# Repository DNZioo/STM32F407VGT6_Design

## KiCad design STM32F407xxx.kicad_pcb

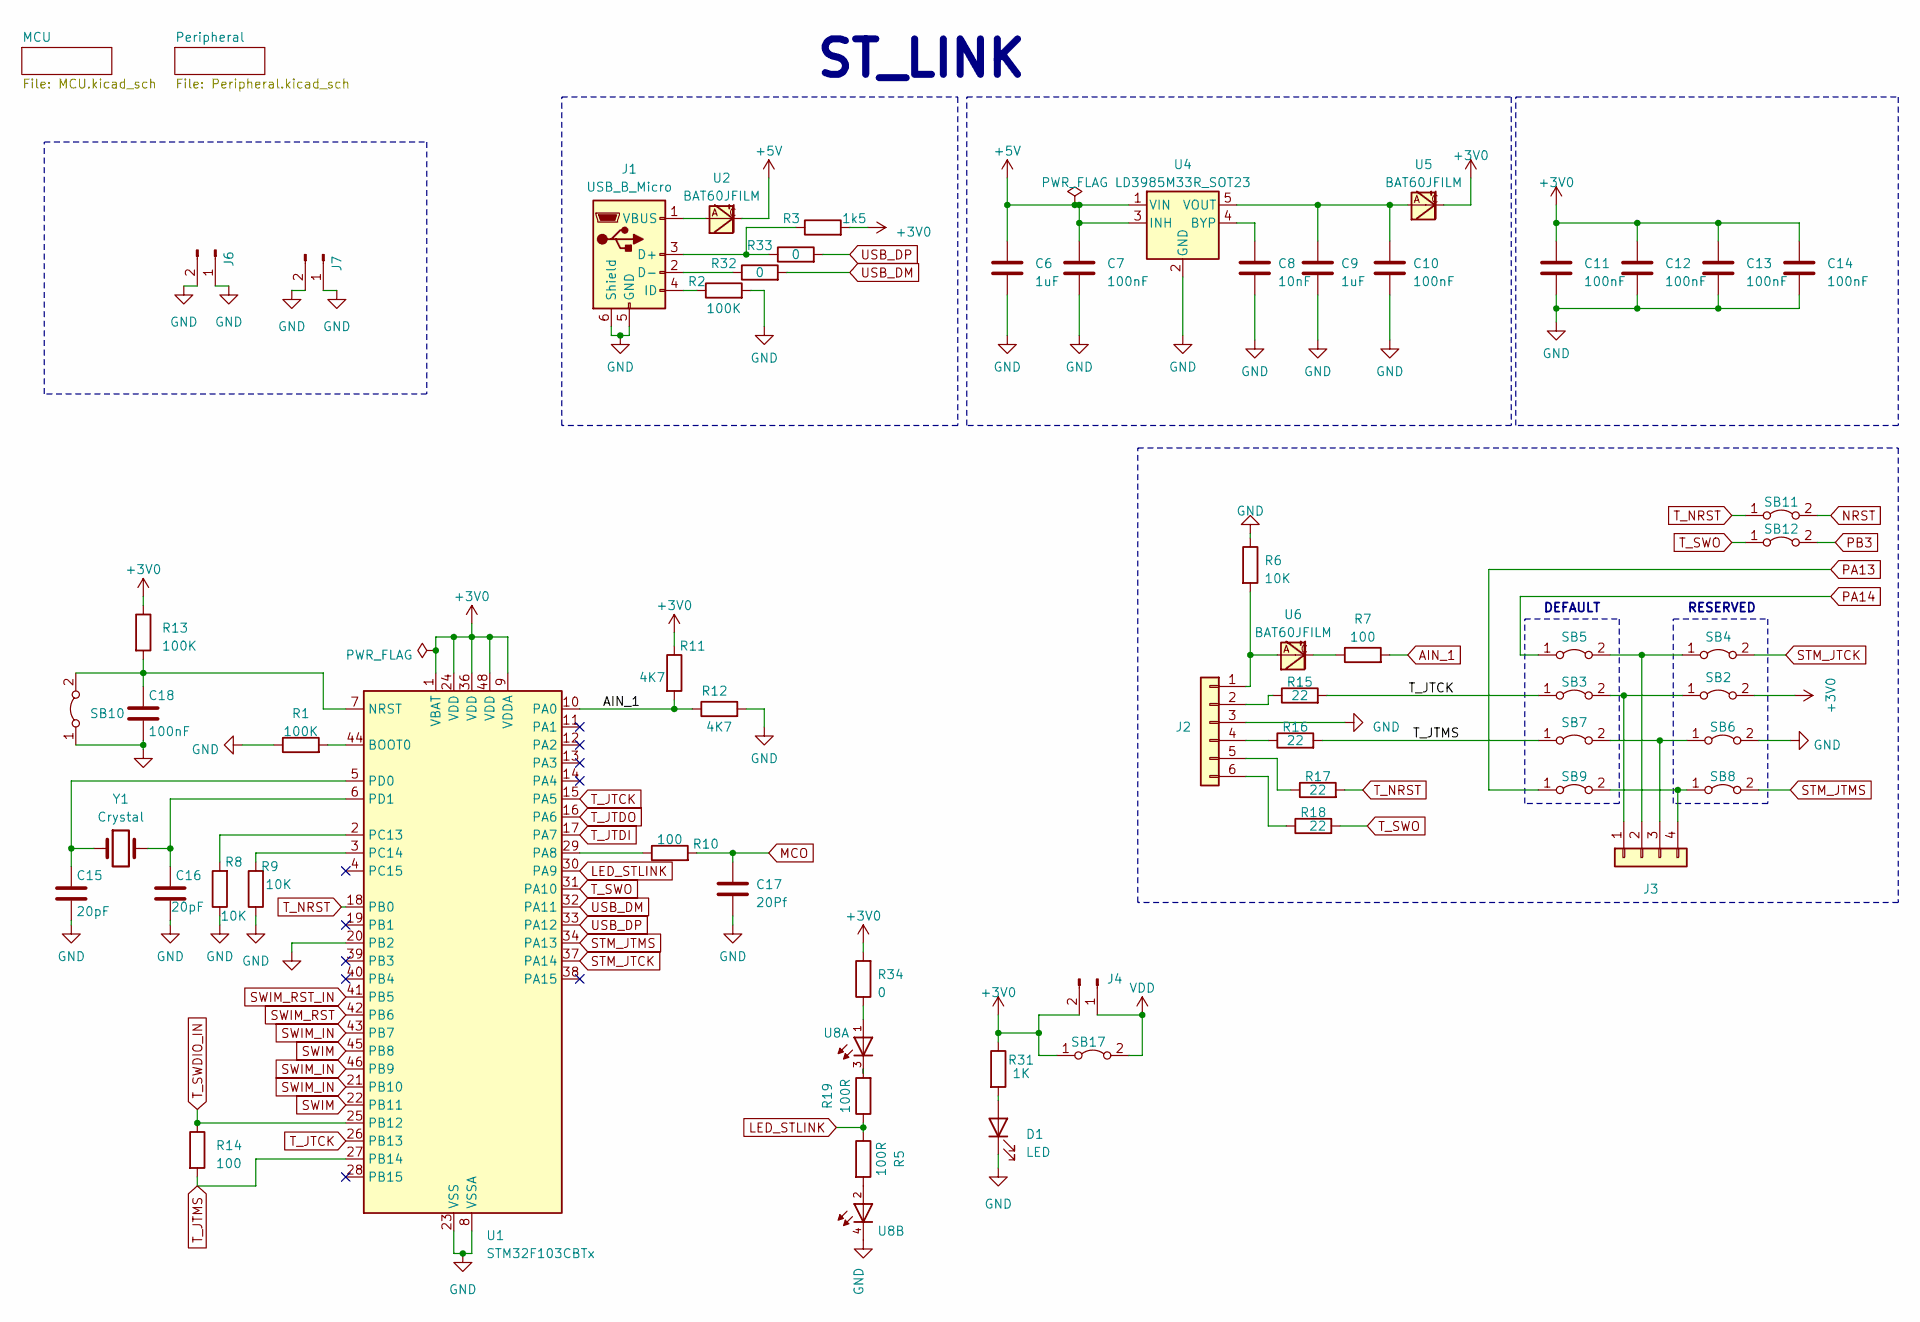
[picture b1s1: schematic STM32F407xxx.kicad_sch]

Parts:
C6, C9: 1uF; C_0603_1608Metric
C7, C10, C11, C12, C13, C14, C18: 100nF; C_0603_1608Metric
C8: 10nF; C_0603_1608Metric
C15, C16: 20pF; C_0603_1608Metric
C17: 20Pf; C_0603_1608Metric
D1: LED; LED_0603_1608Metric
J1: USB_B_Micro; usb_mini
J2: Conn_01x06; PinHeader_1x06_P2.54mm_Vertical
J3: Conn_01x04; PinHeader_1x04_P2.54mm_Vertical
J4, J6, J7: Conn_01x02_Pin; PinHeader_1x02_P2.54mm_Vertical
R1, R2, R13: 100K; R_0603_1608Metric
R3: 1k5; R_0603_1608Metric
R5, R19: 100R; R_0603_1608Metric
R6, R8, R9: 10K; R_0603_1608Metric
R7, R10, R14: 100; R_0603_1608Metric
R11, R12: 4K7; R_0603_1608Metric
R15, R16, R17, R18: 22; R_0603_1608Metric
R31: 1K; R_0603_1608Metric
R32, R33, R34: 0; R_0603_1608Metric
SB2, SB3, SB4, SB5, SB6, SB7, SB8, SB9, SB10, SB11, SB12, SB17: Jumper_2_Bridged; SolderJumper-2_P1.3mm_Open_TrianglePad1.0x1.5mm
U1: STM32F103CBTx; LQFP-48_7x7mm_P0.5mm
U2, U5, U6: BAT60JFILM; SOD323
U4: LD3985M33R_SOT23; SOT-23-5
U8: 150141RB73100; 3528
Y1: Crystal; Crystal_HC49-4H_Vertical

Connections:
+3V0: C11.1, C12.1, C13.1, C14.1, J4.2, R3.2, R11.1, R13.1, R31.1, R34.2, SB2.2 (B), SB17.1 (A), U1.1 (VBAT), U1.9 (VDDA), U1.24 (VDD), U1.36 (VDD), U1.48 (VDD), U5.C; also elsewhere on the board
+5V: C6.1, C7.1, U2.C, U4.1 (VIN), U4.3 (INH); also elsewhere on the board
AIN_1: R7.2, R11.2, R12.1, U1.10 (PA0)
GND: C6.2, C7.2, C8.2, C9.2, C10.2, C11.2, C12.2, C13.2, C14.2, C15.2, C16.2, C17.2, C18.2, D1.1 (K), J1.5 (GND), J1.6 (Shield), J2.3, J6.1, J6.2, J7.1, J7.2, R1.1, R2.2, R6.1, R8.1, R9.1, R12.2, SB6.2 (B), SB10.1 (A), U1.8 (VSSA), U1.20 (PB2), U1.23 (VSS), U1.35 (VSS), U1.47 (VSS), U4.2 (GND), U8.4; also elsewhere on the board
LED_STLINK: R5.1, R19.1, U1.30 (PA9)
MCO: C17.1, R10.2; also elsewhere on the board
NRST: SB11.2 (B); also elsewhere on the board
unnamed: D1.2 (A), R31.2
unnamed: J1.3 (D+), R3.1, R33.1
unnamed: J1.2 (D-), R32.1
unnamed: J1.4 (ID), R2.1
unnamed: J1.1 (VBUS), U2.A
unnamed: J2.1, R6.2, U6.A
unnamed: J2.2, R15.1
unnamed: J2.4, R16.1
unnamed: J2.5, R17.1
unnamed: J2.6, R18.1
unnamed: J3.1, SB2.1 (A), SB3.2 (B)
unnamed: J3.2, SB4.1 (A), SB5.2 (B)
unnamed: J3.3, SB6.1 (A), SB7.2 (B)
unnamed: J3.4, SB8.1 (A), SB9.2 (B)
unnamed: R5.2, U8.2
unnamed: R7.1, U6.C
unnamed: R19.2, U8.3
unnamed: R34.1, U8.1
unnamed: C18.1, R13.2, SB10.2 (B), U1.7 (NRST)
unnamed: R1.2, U1.44 (BOOT0)
unnamed: R10.1, U1.29 (PA8)
unnamed: R8.2, U1.2 (PC13)
unnamed: R9.2, U1.3 (PC14)
unnamed: C15.1, U1.5 (PD0), Y1.1
unnamed: C16.1, U1.6 (PD1), Y1.2
unnamed: C8.1, U4.4 (BYP)
unnamed: C9.1, C10.1, U4.5 (VOUT), U5.A
PA13: SB9.1 (A); also elsewhere on the board
PA14: SB5.1 (A); also elsewhere on the board
PB3: SB12.2 (B); also elsewhere on the board
STM_JTCK: SB4.2 (B), U1.37 (PA14)
STM_JTMS: SB8.2 (B), U1.34 (PA13)
SWIM: U1.22 (PB11), U1.45 (PB8)
SWIM_IN: U1.21 (PB10), U1.43 (PB7), U1.46 (PB9)
SWIM_RST: U1.42 (PB6)
SWIM_RST_IN: U1.41 (PB5)
T_JTCK: R15.2, SB3.1 (A), U1.15 (PA5), U1.26 (PB13)
T_JTDI: U1.17 (PA7)
T_JTDO: U1.16 (PA6)
T_JTMS: R14.2, R16.2, SB7.1 (A), U1.27 (PB14)
T_NRST: R17.2, SB11.1 (A), U1.18 (PB0)
T_SWDIO_IN: R14.1, U1.25 (PB12)
T_SWO: R18.2, SB12.1 (A), U1.31 (PA10)
USB_DM: R32.2, U1.32 (PA11)
USB_DP: R33.2, U1.33 (PA12)
VDD: J4.1, SB17.2 (B); also elsewhere on the board

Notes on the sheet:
DEFAULT
ST_LINK
RESERVED

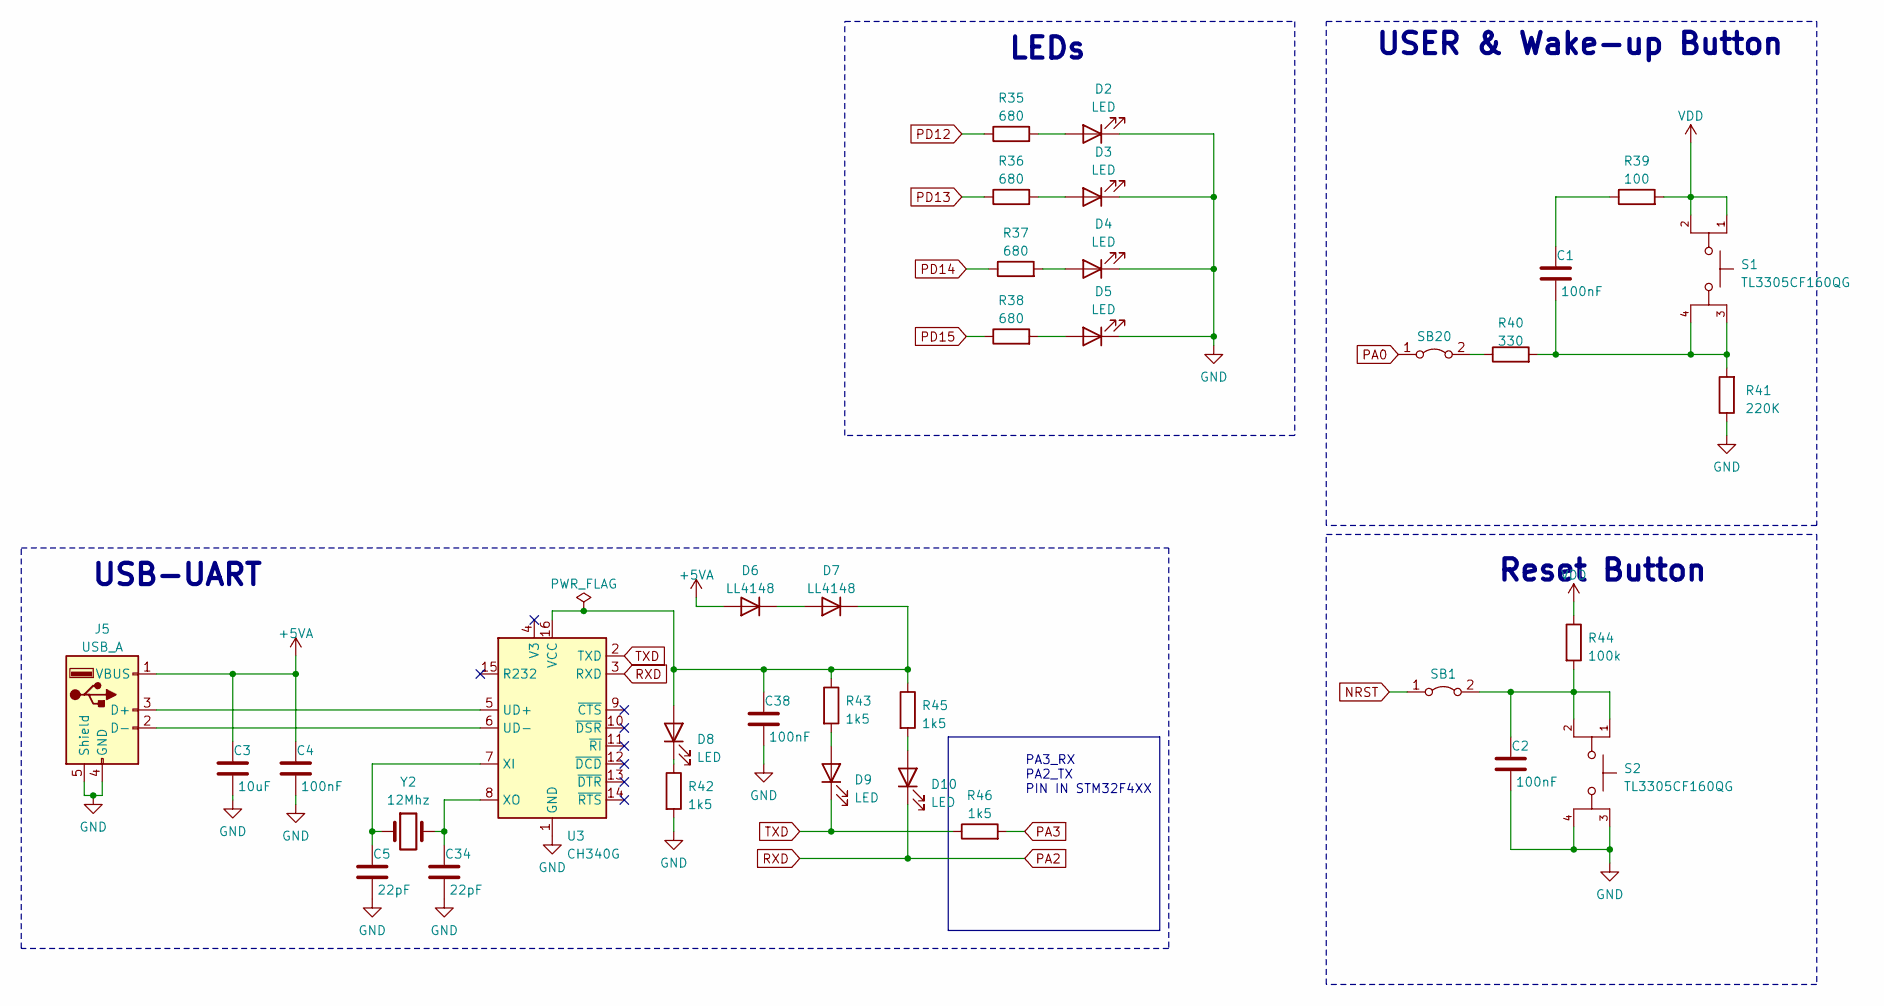
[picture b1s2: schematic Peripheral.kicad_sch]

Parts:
C1, C2, C4, C38: 100nF; C_0603_1608Metric
C3: 10uF; C_0603_1608Metric
C5, C34: 22pF; C_0603_1608Metric
D2, D3, D4, D5, D8, D9, D10: LED; LED_0603_1608Metric
D6, D7: LL4148; D_MiniMELF
J5: USB_A; TE_1981584-1
R35, R36, R37, R38: 680; R_0603_1608Metric
R39: 100; R_0603_1608Metric
R40: 330; R_0603_1608Metric
R41: 220K; R_0603_1608Metric
R42, R43, R45, R46: 1k5; R_0603_1608Metric
R44: 100k; R_0603_1608Metric
S1, S2: TL3305CF160QG; SW_TL3305CF160QG; PARTREV C
SB1, SB20: Jumper_2_Bridged; SolderJumper-2_P1.3mm_Open_TrianglePad1.0x1.5mm
U3: CH340G; SOIC-16_3.9x9.9mm_P1.27mm
Y2: 12Mhz; Crystal_HC49-4H_Vertical

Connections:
+5VA: C3.1, C4.1, D6.2 (A), J5.1 (VBUS)
GND: C2.1, C3.2, C4.2, C5.2, C34.2, C38.2, D2.1 (K), D3.1 (K), D4.1 (K), D5.1 (K), J5.4 (GND), J5.5 (Shield), R41.1, R42.2, S2.3, S2.4, U3.1 (GND); also elsewhere on the board
NRST: SB1.1 (A); also elsewhere on the board
unnamed: C1.1, R40.2, R41.2, S1.3, S1.4
unnamed: C1.2, R39.1
unnamed: D2.2 (A), R35.2
unnamed: D3.2 (A), R36.2
unnamed: D4.2 (A), R37.2
unnamed: D5.2 (A), R38.2
unnamed: D6.1 (K), D7.2 (A)
unnamed: C38.1, D7.1 (K), D8.2 (A), R43.1, R45.1, U3.16 (VCC)
unnamed: D8.1 (K), R42.1
unnamed: D9.2 (A), R43.2
unnamed: D10.2 (A), R45.2
unnamed: J5.3 (D+), U3.5 (UD+)
unnamed: J5.2 (D-), U3.6 (UD-)
unnamed: C2.2, R44.2, S2.1, S2.2, SB1.2 (B)
unnamed: R40.1, SB20.2 (B)
unnamed: C5.1, U3.7 (XI), Y2.1
unnamed: C34.1, U3.8 (XO), Y2.2
PA0: SB20.1 (A); also elsewhere on the board
PA2: D10.1 (K), U3.3 (RXD); also elsewhere on the board
PA3: R46.2; also elsewhere on the board
PD12: R35.1; also elsewhere on the board
PD13: R36.1; also elsewhere on the board
PD14: R37.1; also elsewhere on the board
PD15: R38.1; also elsewhere on the board
TXD: D9.1 (K), R46.1, U3.2 (TXD)
VDD: R39.2, R44.1, S1.1, S1.2; also elsewhere on the board

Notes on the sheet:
LEDs
USER & Wake-up Button
USB-UART
PA3_RX PA2_TX PIN IN STM32F4XX
Reset Button

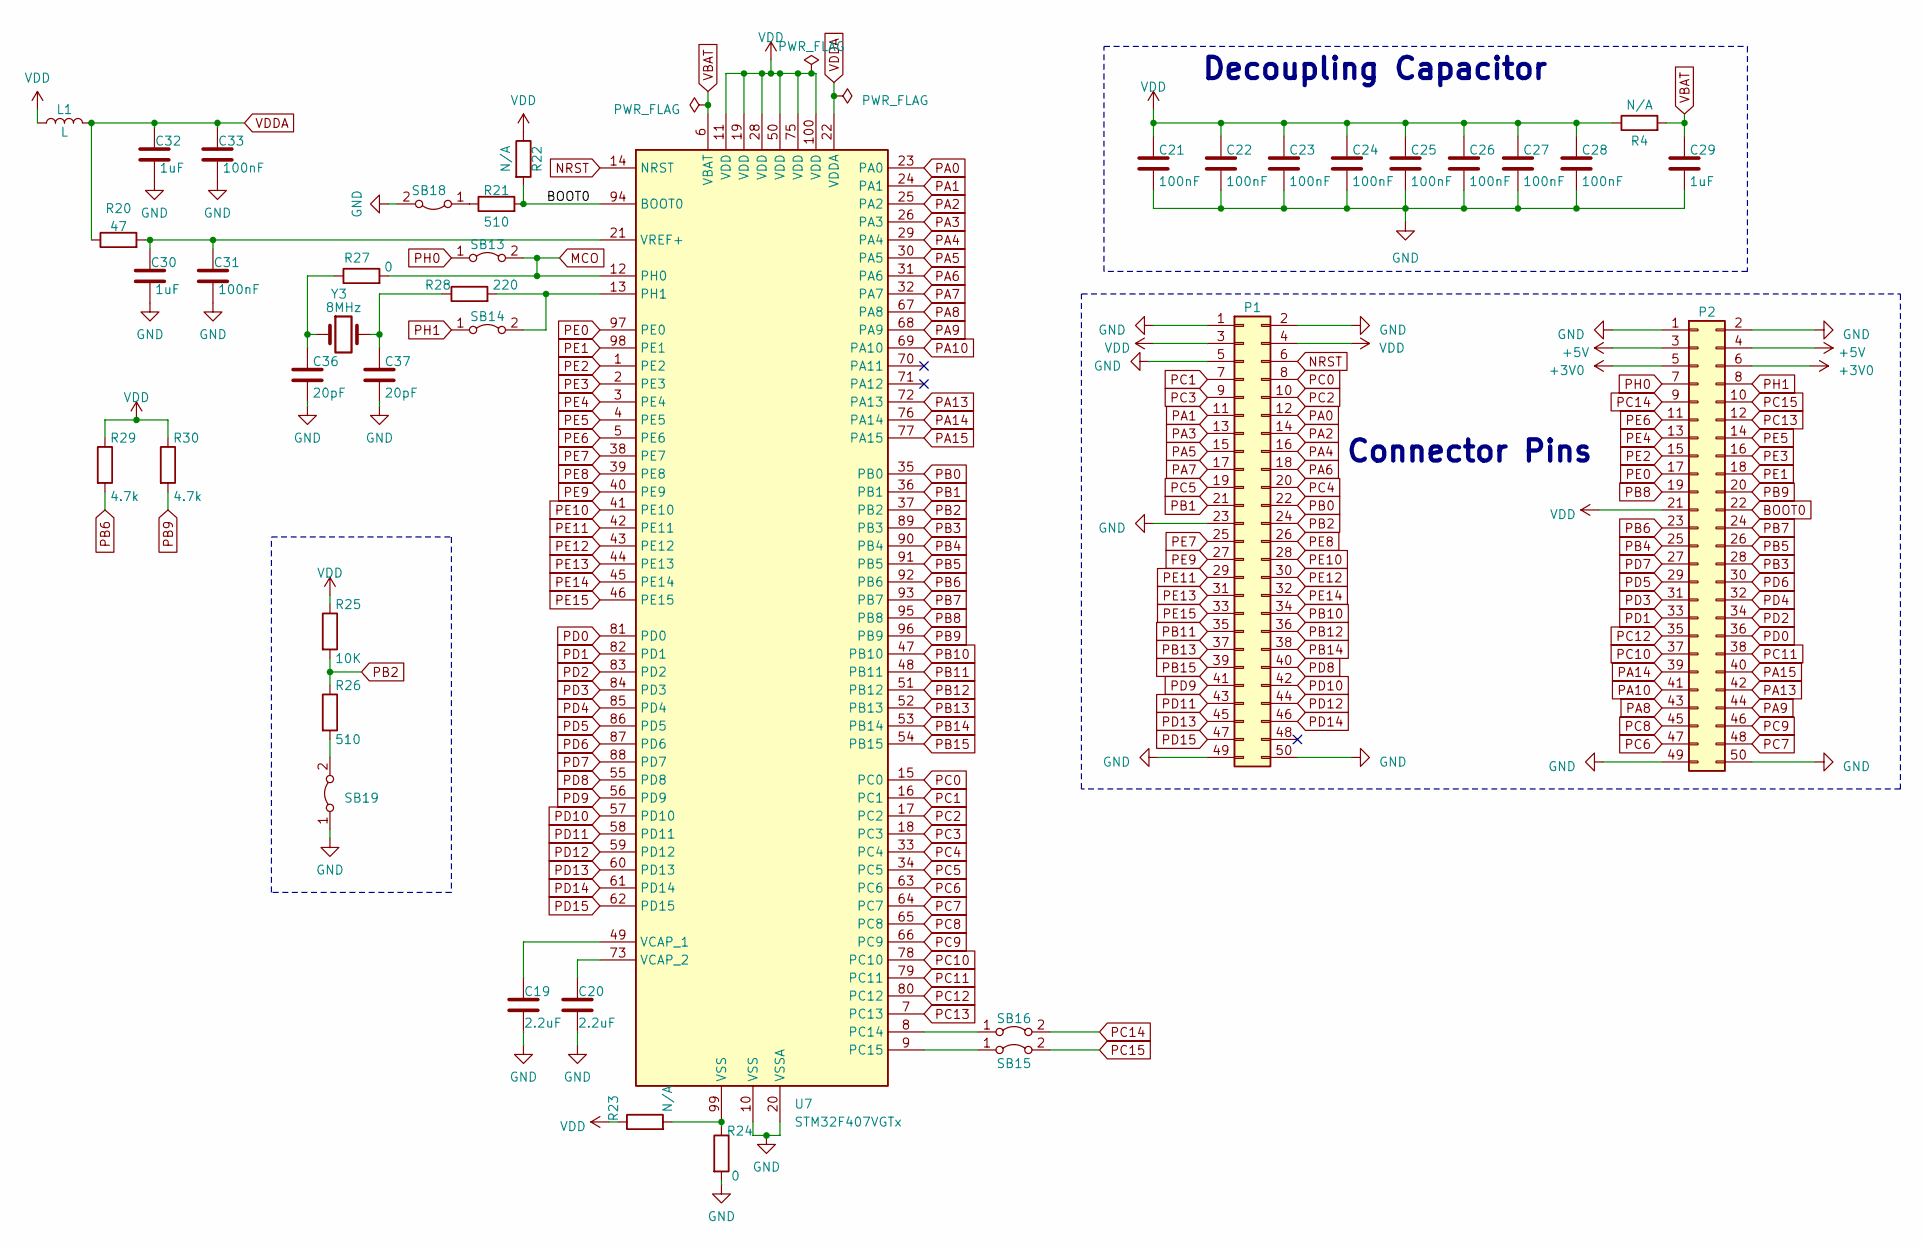
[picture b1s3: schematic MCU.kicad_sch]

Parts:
C19, C20: 2.2uF; C_0603_1608Metric
C21, C22, C23, C24, C25, C26, C27, C28, C31, C33: 100nF; C_0603_1608Metric
C29, C30, C32: 1uF; C_0603_1608Metric
C36, C37: 20pF; C_0603_1608Metric
L1: L; L_0603_1608Metric
P1, P2: Conn_02x25_Odd_Even; PinHeader_2x25_P2.54mm_Vertical
R4, R22, R23: N/A; R_0603_1608Metric
R20: 47; R_0603_1608Metric
R21, R26: 510; R_0603_1608Metric
R24, R27: 0; R_0603_1608Metric
R25: 10K; R_0603_1608Metric
R28: 220; R_0603_1608Metric
R29, R30: 4.7k; R_0603_1608Metric
SB13, SB14, SB15, SB16, SB18, SB19: Jumper_2_Bridged; SolderJumper-2_P1.3mm_Open_TrianglePad1.0x1.5mm
U7: STM32F407VGTx; LQFP-100_14x14mm_P0.5mm
Y3: 8MHz; Crystal_HC49-4H_Vertical

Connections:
+3V0: P2.5, P2.6; also elsewhere on the board
+5V: P2.3, P2.4; also elsewhere on the board
BOOT0: P2.22, R21.2, R22.2, U7.94 (BOOT0)
GND: C19.2, C20.2, C21.2, C22.2, C23.2, C24.2, C25.2, C26.2, C27.2, C28.2, C29.2, C30.2, C31.2, C32.2, C33.2, C36.2, C37.2, P1.1, P1.2, P1.5, P1.23, P1.49, P1.50, P2.1, P2.2, P2.49, P2.50, R24.2, SB18.2 (B), SB19.1 (A), U7.10 (VSS), U7.20 (VSSA), U7.27 (VSS), U7.74 (VSS); also elsewhere on the board
MCO: R27.2, SB13.2 (B), U7.12 (PH0); also elsewhere on the board
NRST: P1.6, U7.14 (NRST); also elsewhere on the board
unnamed: C36.1, R27.1, Y3.1
unnamed: C37.1, R28.1, Y3.2
unnamed: R23.2, R24.1, U7.99 (VSS)
unnamed: R28.2, SB14.2 (B), U7.13 (PH1)
unnamed: SB15.1 (A), U7.9 (PC15)
unnamed: SB16.1 (A), U7.8 (PC14)
unnamed: R21.1, SB18.1 (A)
unnamed: R26.2, SB19.2 (B)
unnamed: C19.1, U7.49 (VCAP_1)
unnamed: C20.1, U7.73 (VCAP_2)
unnamed: C30.1, C31.1, R20.2, U7.21 (VREF+)
PA0: P1.12, U7.23 (PA0); also elsewhere on the board
PA1: P1.11, U7.24 (PA1)
PA2: P1.14, U7.25 (PA2); also elsewhere on the board
PA3: P1.13, U7.26 (PA3); also elsewhere on the board
PA4: P1.16, U7.29 (PA4)
PA5: P1.15, U7.30 (PA5)
PA6: P1.18, U7.31 (PA6)
PA7: P1.17, U7.32 (PA7)
PA8: P2.43, U7.67 (PA8)
PA9: P2.44, U7.68 (PA9)
PA10: P2.41, U7.69 (PA10)
PA13: P2.42, U7.72 (PA13); also elsewhere on the board
PA14: P2.39, U7.76 (PA14); also elsewhere on the board
PA15: P2.40, U7.77 (PA15)
PB0: P1.22, U7.35 (PB0)
PB1: P1.21, U7.36 (PB1)
PB2: P1.24, R25.2, R26.1, U7.37 (PB2)
PB3: P2.28, U7.89 (PB3); also elsewhere on the board
PB4: P2.25, U7.90 (PB4)
PB5: P2.26, U7.91 (PB5)
PB6: P2.23, R29.2, U7.92 (PB6)
PB7: P2.24, U7.93 (PB7)
PB8: P2.19, U7.95 (PB8)
PB9: P2.20, R30.2, U7.96 (PB9)
PB10: P1.34, U7.47 (PB10)
PB11: P1.35, U7.48 (PB11)
PB12: P1.36, U7.51 (PB12)
PB13: P1.37, U7.52 (PB13)
PB14: P1.38, U7.53 (PB14)
PB15: P1.39, U7.54 (PB15)
PC0: P1.8, U7.15 (PC0)
PC1: P1.7, U7.16 (PC1)
PC2: P1.10, U7.17 (PC2)
PC3: P1.9, U7.18 (PC3)
PC4: P1.20, U7.33 (PC4)
PC5: P1.19, U7.34 (PC5)
PC6: P2.47, U7.63 (PC6)
PC7: P2.48, U7.64 (PC7)
PC8: P2.45, U7.65 (PC8)
PC9: P2.46, U7.66 (PC9)
PC10: P2.37, U7.78 (PC10)
PC11: P2.38, U7.79 (PC11)
PC12: P2.35, U7.80 (PC12)
PC13: P2.12, U7.7 (PC13)
PC14: P2.9, SB16.2 (B)
PC15: P2.10, SB15.2 (B)
PD0: P2.36, U7.81 (PD0)
PD1: P2.33, U7.82 (PD1)
PD2: P2.34, U7.83 (PD2)
PD3: P2.31, U7.84 (PD3)
PD4: P2.32, U7.85 (PD4)
PD5: P2.29, U7.86 (PD5)
PD6: P2.30, U7.87 (PD6)
PD7: P2.27, U7.88 (PD7)
PD8: P1.40, U7.55 (PD8)
PD9: P1.41, U7.56 (PD9)
PD10: P1.42, U7.57 (PD10)
PD11: P1.43, U7.58 (PD11)
PD12: P1.44, U7.59 (PD12); also elsewhere on the board
PD13: P1.45, U7.60 (PD13); also elsewhere on the board
PD14: P1.46, U7.61 (PD14); also elsewhere on the board
PD15: P1.47, U7.62 (PD15); also elsewhere on the board
PE0: P2.17, U7.97 (PE0)
PE1: P2.18, U7.98 (PE1)
PE2: P2.15, U7.1 (PE2)
PE3: P2.16, U7.2 (PE3)
PE4: P2.13, U7.3 (PE4)
PE5: P2.14, U7.4 (PE5)
PE6: P2.11, U7.5 (PE6)
PE7: P1.25, U7.38 (PE7)
PE8: P1.26, U7.39 (PE8)
PE9: P1.27, U7.40 (PE9)
PE10: P1.28, U7.41 (PE10)
PE11: P1.29, U7.42 (PE11)
PE12: P1.30, U7.43 (PE12)
PE13: P1.31, U7.44 (PE13)
PE14: P1.32, U7.45 (PE14)
PE15: P1.33, U7.46 (PE15)
PH0: P2.7, SB13.1 (A)
PH1: P2.8, SB14.1 (A)
VBAT: C29.1, R4.2, U7.6 (VBAT)
VDD: C21.1, C22.1, C23.1, C24.1, C25.1, C26.1, C27.1, C28.1, L1.1, P1.3, P1.4, P2.21, R4.1, R22.1, R23.1, R25.1, R29.1, R30.1, U7.11 (VDD), U7.19 (VDD), U7.28 (VDD), U7.50 (VDD), U7.75 (VDD), U7.100 (VDD); also elsewhere on the board
VDDA: C32.1, C33.1, L1.2, R20.1, U7.22 (VDDA)

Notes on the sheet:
Connector Pins
Decoupling Capacitor

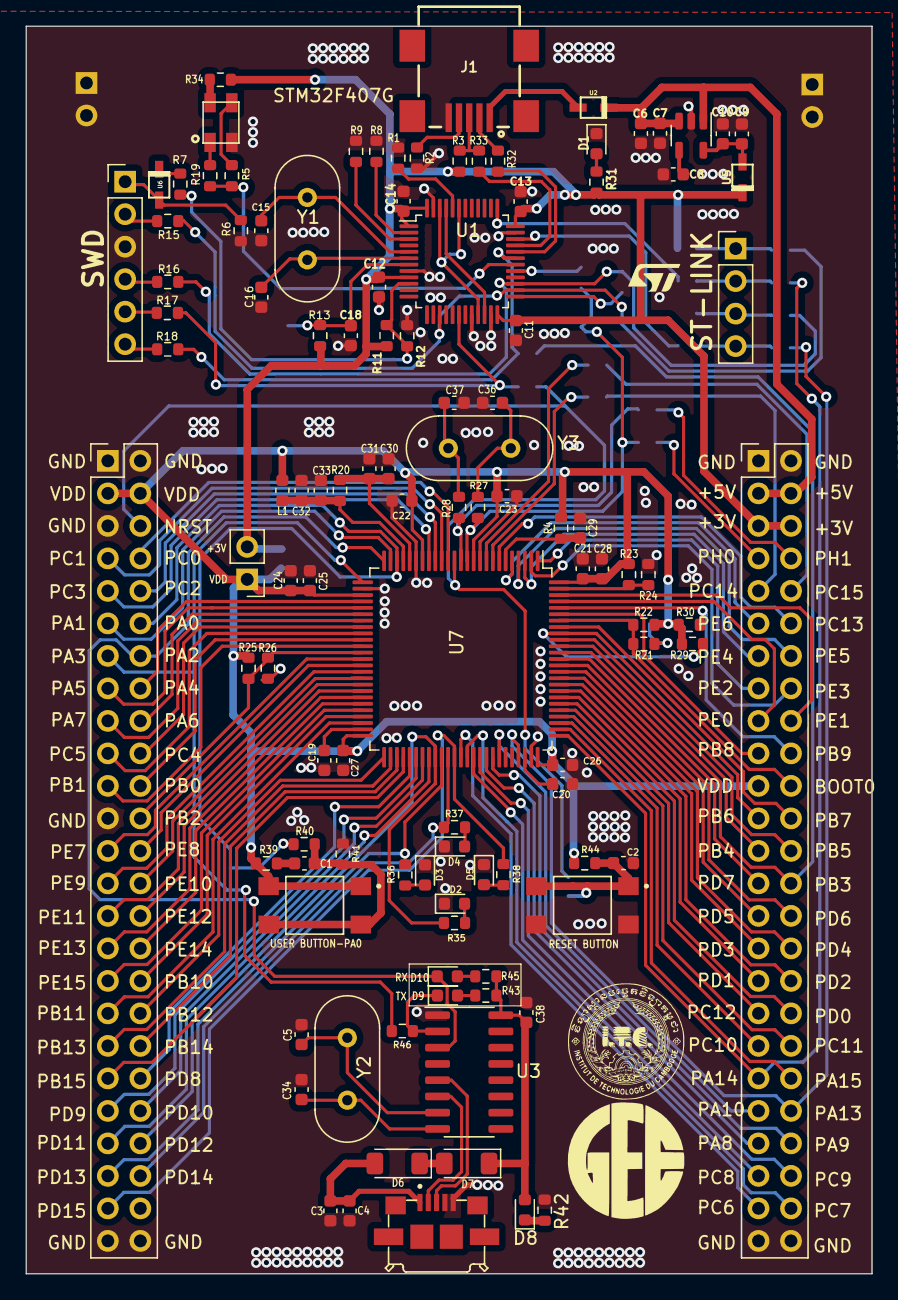
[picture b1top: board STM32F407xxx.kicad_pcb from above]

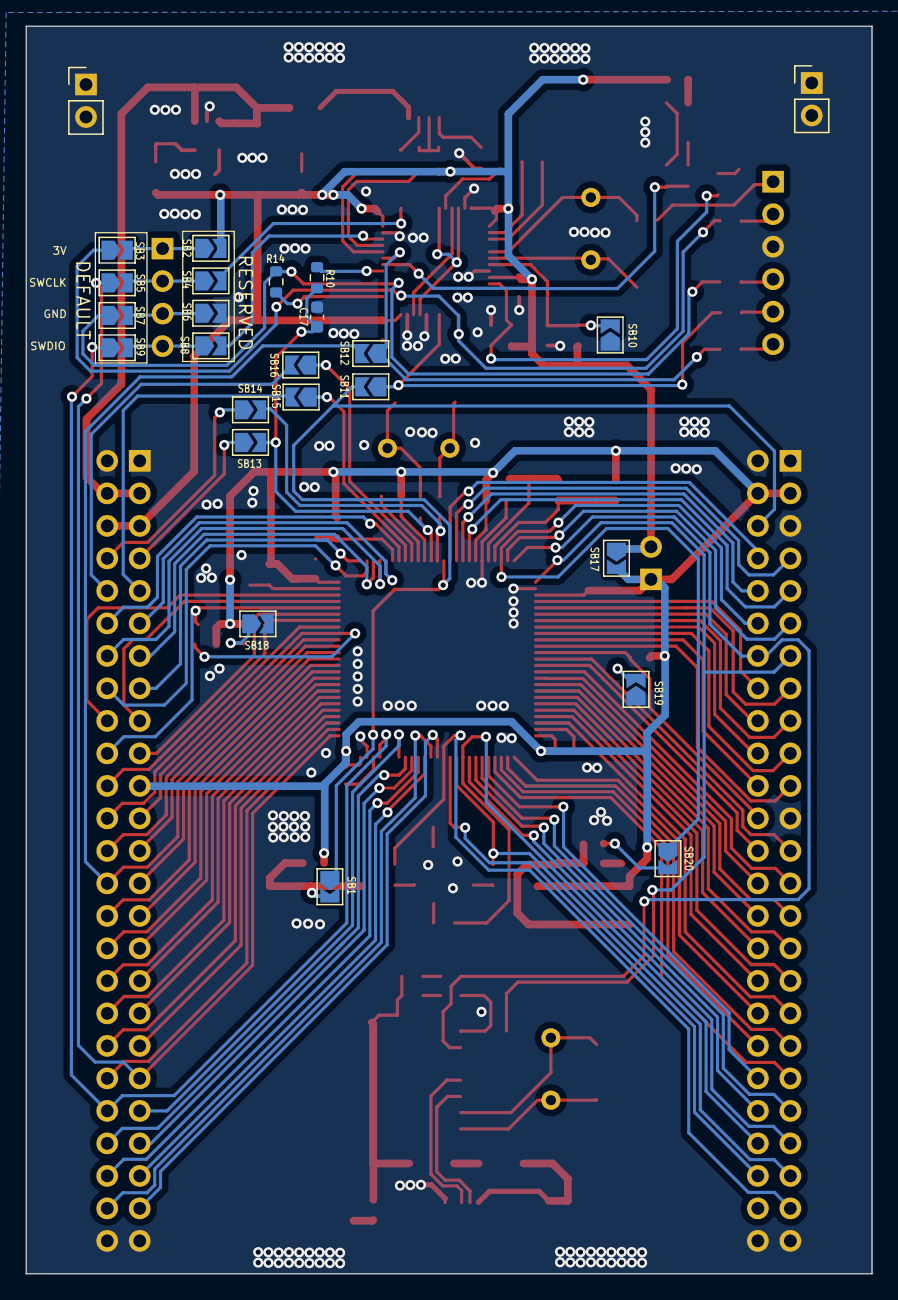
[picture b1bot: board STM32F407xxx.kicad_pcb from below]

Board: 2 copper layers, 66.1 x 97.5 mm, 136 parts (25 on the bottom side), 159 nets.

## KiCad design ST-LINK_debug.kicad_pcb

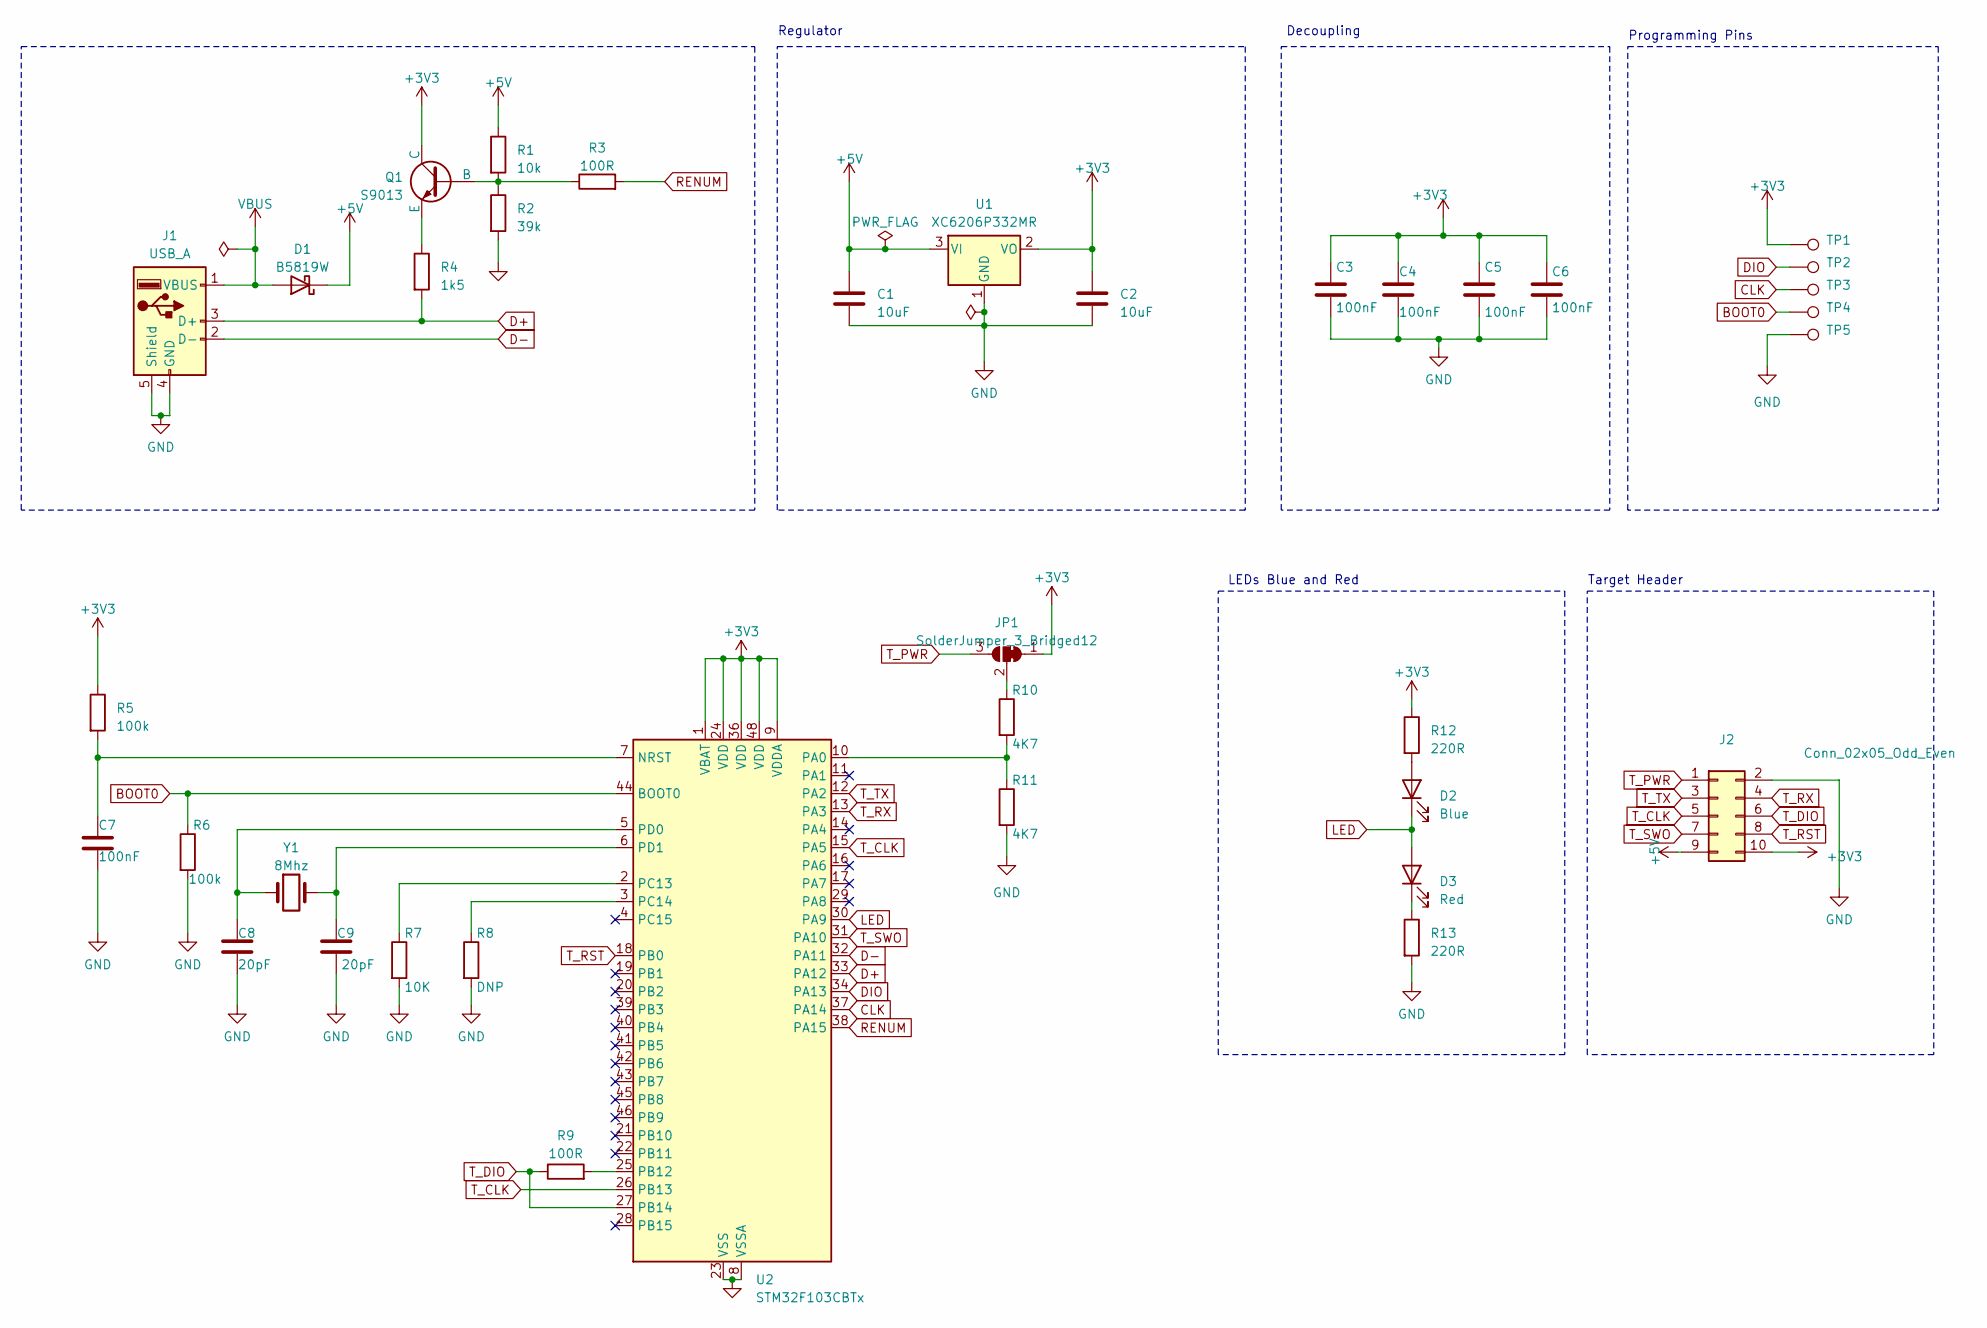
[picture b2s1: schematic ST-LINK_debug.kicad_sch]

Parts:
C1, C2: 10uF; C_0603_1608Metric
C3, C4, C5, C6, C7: 100nF; C_0603_1608Metric
C8, C9: 20pF; C_0603_1608Metric
D1: B5819W; D_SOD-123
D2: Blue; LED_0603_1608Metric
D3: Red; LED_0603_1608Metric
J1: USB_A; USB_Male_A_UP2-AH-1-TH
J2: Conn_02x05_Odd_Even; IDC_EDGE
JP1: SolderJumper_3_Bridged12; SolderJumper-3_P1.3mm_Open_Pad1.0x1.5mm_NumberLabels
Q1: S9013; SOT95P240X120-3N
R1: 10k; R_0603_1608Metric
R2: 39k; R_0603_1608Metric
R3, R9: 100R; R_0603_1608Metric
R4: 1k5; R_0603_1608Metric
R5, R6: 100k; R_0603_1608Metric
R7: 10K; R_0603_1608Metric
R8: DNP; R_0603_1608Metric
R10, R11: 4K7; R_0603_1608Metric
R12, R13: 220R; R_0603_1608Metric
TP1, TP2, TP3, TP4, TP5: TestPoint; TestPoint_Pad_1.0x1.0mm
U1: XC6206P332MR; SOT-23-3
U2: STM32F103CBTx; LQFP-48_7x7mm_P0.5mm
Y1: 8Mhz; Crystal_SMD_5032-2Pin_5.0x3.2mm

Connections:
+3V3: C2.1, C3.1, C4.1, C5.1, C6.1, J2.10, JP1.1 (A), Q1.1 (C), R5.1, R12.1, TP1.1, U1.2 (VO), U2.1 (VBAT), U2.9 (VDDA), U2.24 (VDD), U2.36 (VDD), U2.48 (VDD)
+5V: C1.1, D1.1 (K), J2.9, R1.1, U1.3 (VI)
BOOT0: R6.1, TP4.1, U2.44 (BOOT0)
CLK: TP3.1, U2.37 (PA14)
D+: J1.3 (D+), R4.2, U2.33 (PA12)
D-: J1.2 (D-), U2.32 (PA11)
DIO: TP2.1, U2.34 (PA13)
GND: C1.2, C2.2, C3.2, C4.2, C5.2, C6.2, C7.2, C8.2, C9.2, J1.4 (GND), J1.5 (Shield), J2.2, R2.2, R6.2, R7.2, R8.2, R11.2, R13.2, TP5.1, U1.1 (GND), U2.8 (VSSA), U2.23 (VSS), U2.35 (VSS), U2.47 (VSS)
LED: D2.1 (K), D3.2 (A), U2.30 (PA9)
unnamed: D2.2 (A), R12.2
unnamed: D3.1 (K), R13.1
unnamed: JP1.2 (C), R10.1
unnamed: Q1.2 (B), R1.2, R2.1, R3.1
unnamed: Q1.3 (E), R4.1
unnamed: C7.1, R5.2, U2.7 (NRST)
unnamed: R10.2, R11.1, U2.10 (PA0)
unnamed: R9.2, U2.25 (PB12)
unnamed: R7.1, U2.2 (PC13)
unnamed: R8.1, U2.3 (PC14)
unnamed: C8.1, U2.5 (PD0), Y1.1
unnamed: C9.1, U2.6 (PD1), Y1.2
RENUM: R3.2, U2.38 (PA15)
T_CLK: J2.5, U2.15 (PA5), U2.26 (PB13)
T_DIO: J2.6, R9.1, U2.27 (PB14)
T_PWR: J2.1, JP1.3 (B)
T_RST: J2.8, U2.18 (PB0)
T_RX: J2.4, U2.13 (PA3)
T_SWO: J2.7, U2.31 (PA10)
T_TX: J2.3, U2.12 (PA2)
VBUS: D1.2 (A), J1.1 (VBUS)

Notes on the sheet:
Target Header
Regulator
LEDs Blue and Red
Programming Pins
Decoupling

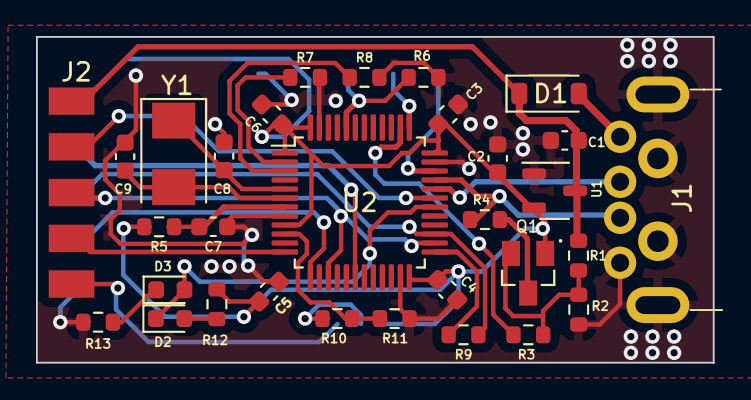
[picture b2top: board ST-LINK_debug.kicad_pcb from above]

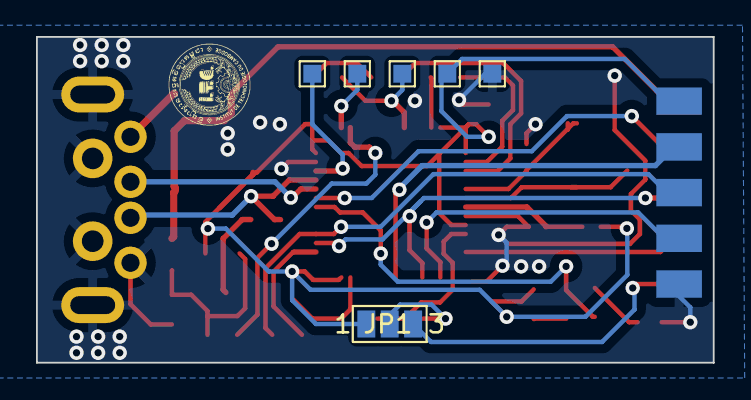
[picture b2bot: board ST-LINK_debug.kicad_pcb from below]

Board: 2 copper layers, 37.6 x 18.1 mm, 37 parts (6 on the bottom side), 30 nets.

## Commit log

2023-11-19 final file
2023-12-19 attiny85_USB.kicad_pattiny85_USB.kicad_prlcb
2023-12-19 Second commit
